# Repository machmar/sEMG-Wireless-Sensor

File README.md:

# sEMG Wireless Sensor

This repository contains the code and hardware design files for a **wireless surface electromyography (sEMG) sensor**, developed as part of my Bachelor's thesis.

The device is designed to measure muscle activity using non-invasive surface electrodes and transmit the data wirelessly for real-time monitoring and analysis.

Its primary purpose is to assist during exercise by providing greater insight into individual muscle activation and strain.

---
<sub>This file was originally generated with the assistance of AI (ChatGPT) and subsequently reviewed and edited by a human.</sub>

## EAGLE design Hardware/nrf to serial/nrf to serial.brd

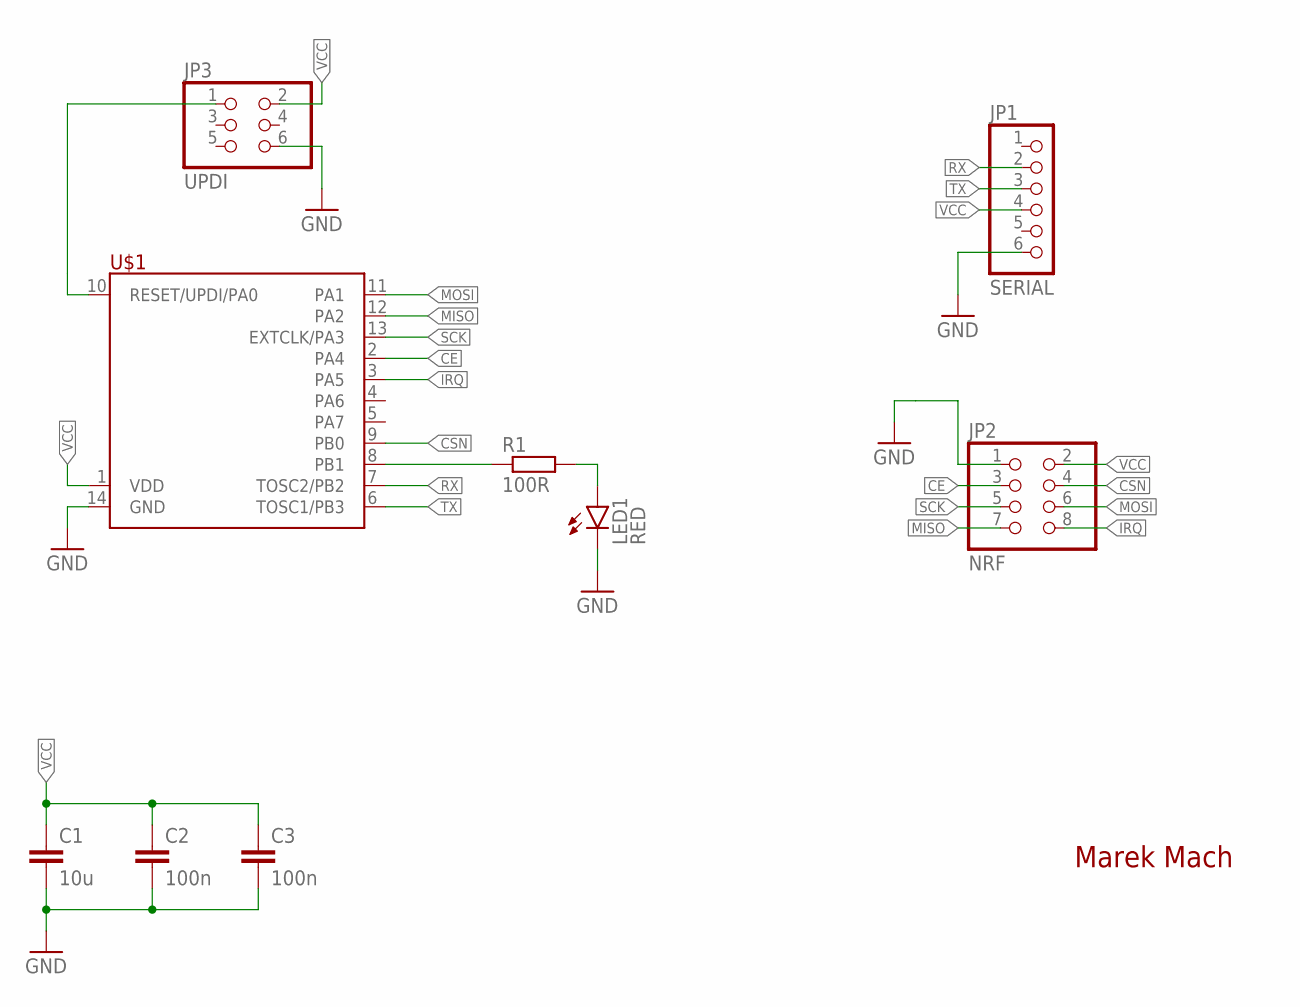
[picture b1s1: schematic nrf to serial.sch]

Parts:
C1: 10u; C0603
C2, C3: 100n; C0603
JP1: SERIAL; 1X06
JP2: NRF; 2X04
JP3: UPDI; 2X03
LED1: RED; LED3MM
R1: 100R; R0603
U$1: TINY214/414/814SOIC; SOIC14

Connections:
CE: JP2.3, U$1.2 (PA4)
CSN: JP2.4, U$1.9 (PB0)
GND: C1.2, C2.2, C3.2, JP1.6, JP2.1, JP3.6, LED1.K (C), U$1.14 (GND)
IRQ: JP2.8, U$1.3 (PA5)
MISO: JP2.7, U$1.12 (PA2)
MOSI: JP2.6, U$1.11 (PA1)
unnamed: R1.1, U$1.8 (PB1)
unnamed: JP3.1, U$1.10 (RESET/UPDI/PA0)
unnamed: LED1.A, R1.2
RX: JP1.2, U$1.7 (TOSC2/PB2)
SCK: JP2.5, U$1.13 (EXTCLK/PA3)
TX: JP1.3, U$1.6 (TOSC1/PB3)
VCC: C1.1, C2.1, C3.1, JP1.4, JP2.2, JP3.2, U$1.1 (VDD)

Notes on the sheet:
Marek Mach

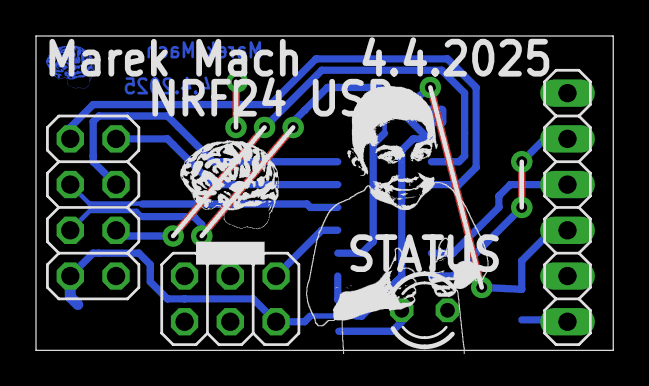
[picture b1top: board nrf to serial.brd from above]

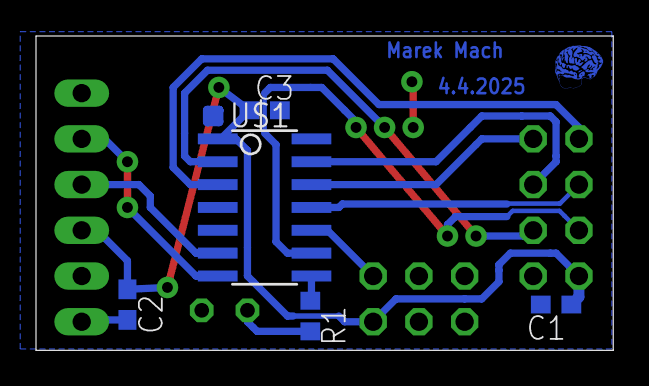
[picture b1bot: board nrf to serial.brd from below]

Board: 2 copper layers, 32.1 x 17.5 mm, 9 parts (5 on the bottom side), 13 nets.

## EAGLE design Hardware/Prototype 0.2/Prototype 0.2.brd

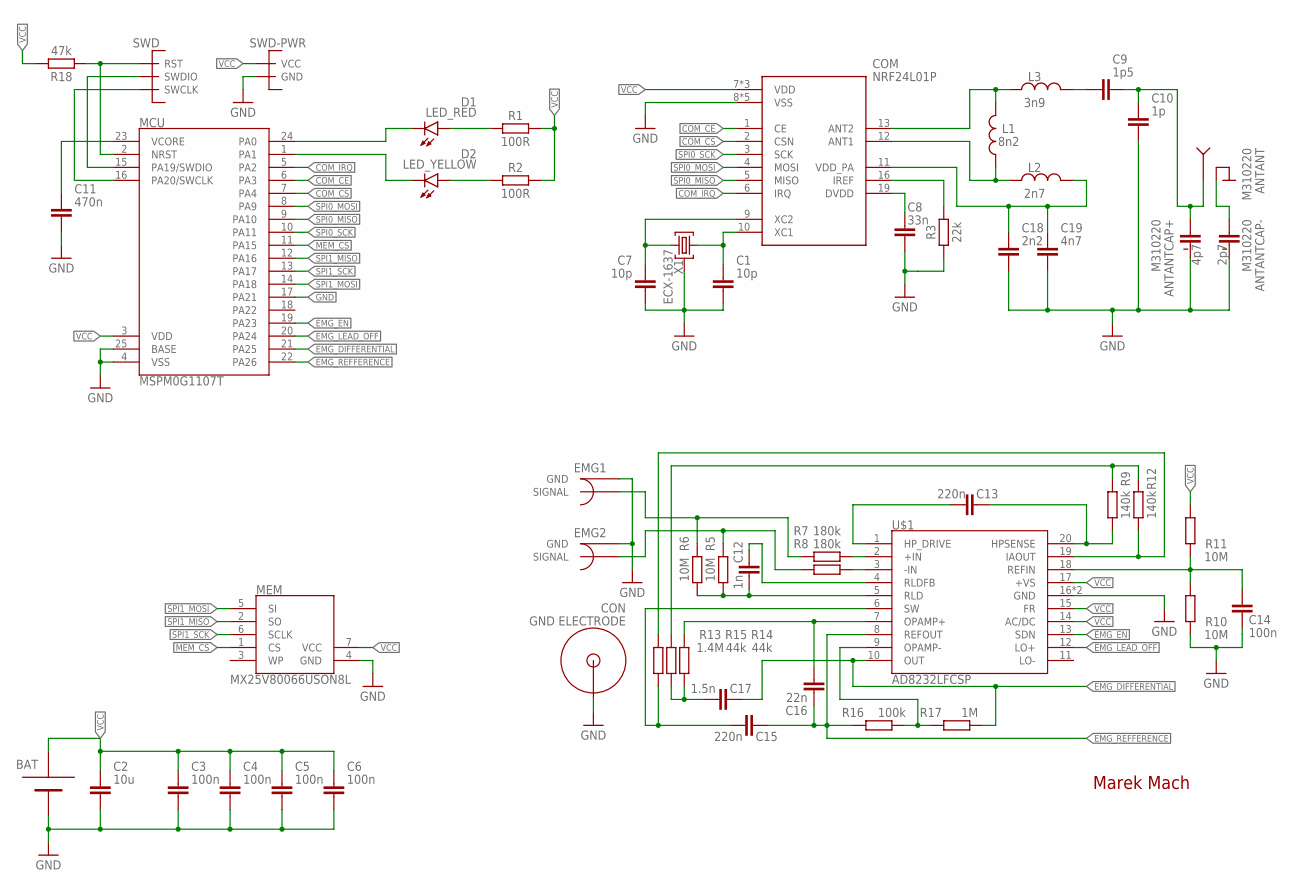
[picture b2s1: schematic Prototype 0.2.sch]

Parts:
ANT: M310220
BAT: 2025BAT-HLD-005-THM; BAT-HLD-005-THM
C1, C7: 10p; CAPC1005X60
C2: 10u; CAPC1608X85
C3, C4, C5, C6, C14: 100n; CAPC1608X85
C8: 33n; CAPC1005X60
C9: 1p5; CAPC1005X60
C10: 1p; CAPC1005X60
C11: 470n; CAPC1608X85
C12: 1n; CAPC1608X85
C13, C15: 220n; CAPC1608X85
C16: 22n; CAPC1608X85
C17: 1.5n; CAPC1608X85
C18: 2n2; CAPC1005X60
C19: 4n7; CAPC1005X60
COM: NRF24L01P; QFN50P400X400X100-21T265
CON: GND ELECTRODE; ELECTRODE_CONNECTOR
D1: LED_RED; LEDC1005X25N_FLAT-R
D2: LED_YELLOW; LEDC1005X25N_FLAT-Y
EMG1, EMG2: SHIELDED-CONNECTOR; SHIELDED-SMD
L1: 8n2; INDC1006X60N
L2: 2n7; INDC1006X60N
L3: 3n9; INDC1006X60N
MCU: MSPM0G1107T; QFN50P400X400X100-25T240
MEM: MX25V80066USON8L; SON50P300X200X50-8
R1, R2: 100R; RESC1608X60
R3: 22k; RESC1005X40
R5, R6, R10, R11: 10M; RESC1608X60
R7, R8: 180k; RESC1608X60
R9, R12: 140k; RESC1608X60
R13: 1.4M; RESC1608X60
R14, R15: 44k; RESC1608X60
R16: 100k; RESC1608X60
R17: 1M; RESC1608X60
R18: 47k; RESC1608X60
SWD: SWD; 3X
SWD-PWR: PWR; 2X
U$1: AD8232LFCSP; QFN50P400X400X80-21T275
X1: ECX-1637; WE-XTAL_IQXC-42

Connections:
COM_CE: COM.1 (CE), MCU.6 (PA3)
COM_CS: COM.2 (CSN), MCU.7 (PA4)
COM_IRQ: COM.6 (IRQ), MCU.5 (PA2)
EMG_DIFFERENTIAL: C17.2, MCU.21 (PA25), R17.1, U$1.10 (OUT)
EMG_EN: MCU.19 (PA23), U$1.13 (SDN)
EMG_LEAD_OFF: MCU.20 (PA24), U$1.12 (LO+)
EMG_REFFERENCE: C15.2, C16.1, MCU.22 (PA26), R16.2, U$1.8 (REFOUT)
GND: ANT.FEEDCAP-GND (NEG), ANT.GNDCAP-GND (NEG), BAT.P$1 (-), C1.2, C2.2, C3.2, C4.2, C5.2, C6.2, C7.2, C8.2, C10.2, C11.2, C14.1, C18.2, C19.2, COM.8 (VSS), COM.14 (VSS), COM.17 (VSS), COM.20 (VSS), COM.21 (VSS), CON.P$1, CON.P$2, CON.P$3, CON.P$4, EMG1.GND1 (GND), EMG1.GND2 (GND), EMG2.GND1 (GND), EMG2.GND2 (GND), MCU.4 (VSS), MCU.17 (PA21), MCU.25 (BASE), MEM.4 (GND), R3.1, R10.1, SWD-PWR.1 (GND), U$1.16 (GND), U$1.21 (GND), X1.2 (GND), X1.4 (GND)
MEM_CS: MCU.11 (PA15), MEM.1 (CS)
unnamed: C1.1, COM.10 (XC1), X1.1
unnamed: C11.1, MCU.23 (VCORE)
unnamed: D1.A, R1.1
unnamed: D2.A, R2.1
unnamed: C7.1, COM.9 (XC2), X1.3 (2)
unnamed: ANT.GNDCAP-GROUND (POS), ANT.GROUND
unnamed: C8.1, COM.19 (DVDD)
unnamed: COM.13 (ANT2), L1.2, L3.1
unnamed: C9.1, L3.2
unnamed: EMG1.SIG (SIGNAL), R6.2, R7.2
unnamed: EMG2.SIG (SIGNAL), R5.2, R8.2
unnamed: R7.1, U$1.2 (+IN)
unnamed: R8.1, U$1.3 (-IN)
unnamed: C16.2, R14.1, U$1.7 (OPAMP+)
unnamed: R16.1, R17.2, U$1.9 (OPAMP-)
unnamed: R9.2, R12.2, R15.2
unnamed: C12.1, R5.1, R6.1, U$1.5 (RLD)
unnamed: C13.1, U$1.1 (HP_DRIVE)
unnamed: C13.2, R9.1, U$1.20 (HPSENSE)
unnamed: COM.16 (IREF), R3.2
unnamed: C14.2, R10.2, R11.1, U$1.18 (REFIN)
unnamed: COM.12 (ANT1), L1.1, L2.1
unnamed: C15.1, R13.2, U$1.6 (SW)
unnamed: C17.1, R14.2, R15.1
unnamed: R12.1, R13.1, U$1.19 (IAOUT)
unnamed: C12.2, U$1.4 (RLDFB)
unnamed: ANT.FEED (ANTENNA), ANT.FEEDCAP-ANT (POS), C9.2, C10.1
unnamed: C18.1, C19.1, COM.11 (VDD_PA), L2.2
RED-STATUS-LED: D1.C, MCU.24 (PA0)
RST: MCU.2 (NRST), R18.1, SWD.1 (RST)
SPI0_MISO: COM.5 (MISO), MCU.9 (PA10)
SPI0_MOSI: COM.4 (MOSI), MCU.8 (PA9)
SPI0_SCK: COM.3 (SCK), MCU.10 (PA11)
SPI1_MISO: MCU.12 (PA16), MEM.2 (SO)
SPI1_MOSI: MCU.14 (PA18), MEM.5 (SI)
SPI1_SCK: MCU.13 (PA17), MEM.6 (SCLK)
SWCLK: MCU.16 (PA20/SWCLK), SWD.3 (SWCLK)
SWDIO: MCU.15 (PA19/SWDIO), SWD.2 (SWDIO)
VCC: BAT.P$2 (+), BAT.P$3 (+), C2.1, C3.1, C4.1, C5.1, C6.1, COM.7 (VDD), COM.15 (VDD), COM.18 (VDD), MCU.3 (VDD), MEM.7 (VCC), R1.2, R2.2, R11.2, R18.2, SWD-PWR.2 (VCC), U$1.14 (AC/DC), U$1.15 (FR), U$1.17 (+VS)
YELLOW-STATUS-LED: D2.C, MCU.1 (PA1)

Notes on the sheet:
Marek Mach
4p7
2p7

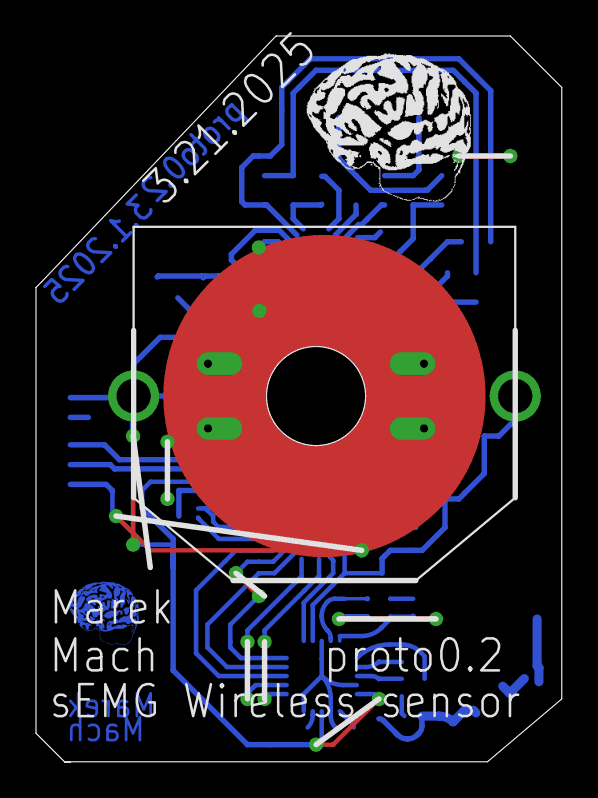
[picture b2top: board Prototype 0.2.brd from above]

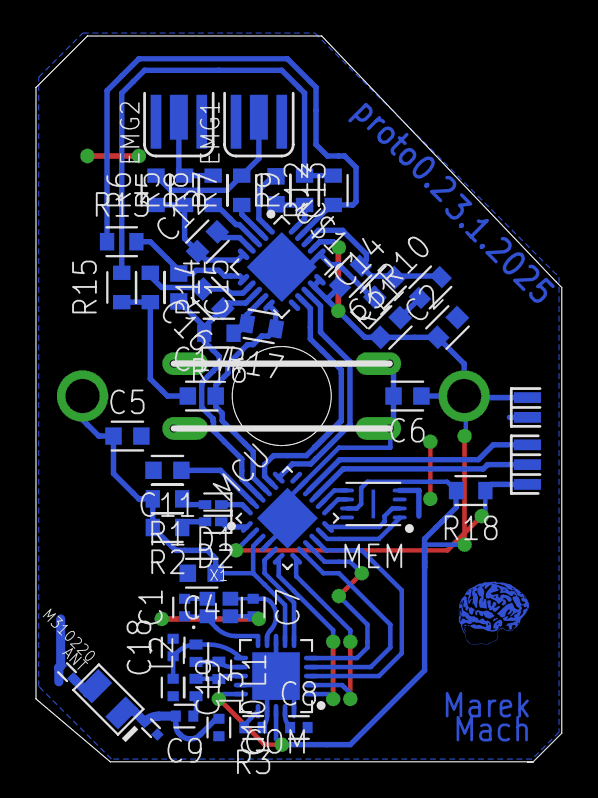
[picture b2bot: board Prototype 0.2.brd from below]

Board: 2 copper layers, 29.2 x 40.3 mm, 53 parts (52 on the bottom side), 49 nets.

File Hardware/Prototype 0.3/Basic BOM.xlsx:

name | count | status | # | value | package
Sensor
R1, R2 | 2 | Ordered | 100 | 100R | 0402
R18 | 1 | Ordered | 20 | 47k | 0402
C11 | 1 | Missing |  | 270n | 0402
D1 | 1 | At home | 8 | Red | 0402
D2 | 1 | At home | 7 | Yellow | 0402
C7, C1 | 2 | At home | 8 | 10p | 0402
C8 | 1 | At home | 99 | 33n 10% | 0402
R3 | 1 | At home | 100 | 22k 1% | 0402
L1 | 1 | At home | 9 | 8n2H | 0402
L2 | 1 | At home | 9 | 2n7H | 0402
L3 | 1 | At home | 9 | 3n9H | 0402
C9 | 1 | Ordered | 20 | 1p5 0.1p | 0402 | only have 0.25pf tolerance
C10 | 1 | Ordered | 20 | 1p 0.1p | 0402
C18 | 1 | At home | 19 | 2n2 10% | 0402
C19 | 1 | At home | 19 | 4p7 0.25p | 0402
AntCap+ | 1 | Ordered | 20 | 5p1 0.05p | 0402
AntCap- | 1 | At home | 19 | 2p7 0.05p | 0402
X1 | 1 | At home | 4 | 16Mhz | --
R6, R5, R10, R11 | 4 | At home | 96 | 10M | 0402
R7, R8 | 2 | Ordered | 20 | 180k | 0402
R13 | 1 | Missing |  | 1M4 | 0402
R15, R14 | 2 | Missing |  | 44k | 0402
C17 | 1 | Ordered | 20 | 1n5 | 0402
C15, C13 | 2 | Ordered | 20 | 220n | 0402
C16 | 1 | Ordered | 20 | 22n | 0402
R16 | 1 | Ordered | 100 | 100k | 0402
R17 | 1 | Ordered | 100 | 1M | 0402
R9, R12 | 2 | Missing |  | 140k | 0402
C12 | 1 | Ordered | 20 | 1n | 0402
C2 | 1 | At home | 10 | 10u | 0402
C3, C4, C5, C6, C14, C21, C22 | 7 | Ordered | 100 | 100n | 0402
D | 1 | At home | 10 | DFN1006 | --
F1 | 1 | At home | 10 | 40mA | --
F2 | 1 | At home | 10 | PESD3V3 | --
BAT | 1 | At home | 7 | 2032 hldr | --
MEM | 1 | Missing |  | MXV25V80066 | USON8L | got some other to test
MCU | 1 | Missing |  | MSPM0G1107T | QFN24
COM | 1 | At home | 1 | NRF24L01+ | QFN20
AMP | 1 | Missing | 0 | AD8232 | QFN20
EMG1 | 1 | At home | 10 | steel wire | 0.35mm
Antenna | 1 | At home | 2 | Kyocera M310220 | --
name | count | status | # | value | package
Receiver
MCU | 1 | Ordered | 13 | attiny814 | SOIC14
R1 | 1 | At home | 80 | 100R | 0603
C1 | 1 | At home | 20 | 10u | 0603
C2, C3 | 2 | At home | 100 | 100n | 0603
LED1 | 1 | At home | 100 | Red | 3mm
R2 | 1 | At home | 100 | 10k | 0603 | (for reset pin to vcc)
UART | 1 | Ordered | 3 | FT232 | --
USB | 1 | At home | 5 | some micro (lazy) | --
LED2, LED3 | 2 | At home | 20 | red | 0603
R3, R4 | 2 | At home | 20 | 330R | 0603
FERR | 1 | Ordered | 10 | -- | 0603

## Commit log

2025-03-08 initial, off detection works
2025-03-09 Switched to sysconfig initialization
2025-03-09 Updated gitignore
2025-03-28 porting to proto0.2
2025-03-28 Fixed port mapping
2025-03-29 NRF sends basic data succesfully
2025-03-29 Sending raw ADC data each whatever seconds
2025-04-05 Added header for hardware controls
2025-04-05 Working on nrf driver
2025-04-06 pipe setting is broken but transmitting works
2025-04-06 deleted debug folder
2025-04-06 restore deleted files besides debug
2025-04-06 make sensorSide folder
2025-04-06 Moved
2025-04-06 Added PC side
2025-04-06 Basic coms work!
2025-04-06 cleanup
2025-04-06 fixed overflow issue
2025-04-06 added random notes and such
2025-04-09 fixed junk data, baud set to 1000000
2025-04-09 Adding data transmission (to sensor)
2025-04-09 added proper commands (previous data was junk)
2025-04-09 I forgot to commit for the entire day 💀
2025-04-10 Fixed crashes by slowing down SPI
2025-04-10 Transmitter is probably done I think
2025-04-10 adding ADC interrupt
2025-04-10 Nulls can be transmitted with manual length control
2025-04-10 changed JTAG to 200kHz
2025-04-10 forgot debugging thing
2025-04-10 Added a 1ms interrupt (ADC based)
2025-04-10 Added millis
2025-04-10 Send data quicker
2025-04-10 Added chatgpts visualization app
2025-04-10 migrated to pyqtgraph
2025-04-10 added difference graph
2025-04-10 added peak line and left info bar
2025-04-10 added RMS line
2025-04-10 made three plots
2025-04-10 added buttons, only Reset works
2025-04-10 Made the transmitted packet "official"
2025-04-10 added notes about measurement start and stop
2025-04-10 made flash quicker
2025-04-10 Renamed enum states
2025-04-11 Basic two way communication established
2025-04-11 correct sending to sensor
2025-04-11 Added receiver error and state codes, implemented
2025-04-11 Added state/error display and handling
2025-04-11 made sidebar resizable, bit more organized
2025-04-11 SPI speed @4MHz
2025-04-11 added emg message frequency counter
2025-04-11 transmits 5 samples at a time
    total transfer @500Hz now
2025-04-11 Added a file for random notes
2025-04-11 app is functional enough with the new frequency
2025-04-11 Added basic responses to commands
2025-04-11 edit plot scaling
2025-04-11 Adding actual two way coms
2025-04-11 Added interrupt timeout
2025-04-11 automatically send electrode state
2025-04-12 moved fifo reactions around a bit
2025-04-12 forgot to revert to normal transmit speed
2025-04-12 ignores incorrectly read values
2025-04-12 ignore reference value under 1000
2025-04-12 ignore values over 3000 as well
2025-04-12 added hardware design files
2025-04-12 Create LICENSE
2025-04-12 Create LICENSE_HARDWARE
2025-04-12 Added a notice of AI usage
2025-04-12 Added a simple readme
2025-04-13 added dependecies list
2025-04-17 added a simple BOM
2025-04-18 Started implementing the Flash memory
2025-04-19 Added flash and some tests
